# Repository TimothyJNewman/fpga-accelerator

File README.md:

# fpga-accelerator
Creating an FPGA image processor using the Lattice Crosslink-NX LIFCL-40 FPGA. The form factor is a raspberry pi hat.

Using KICAD version 7.

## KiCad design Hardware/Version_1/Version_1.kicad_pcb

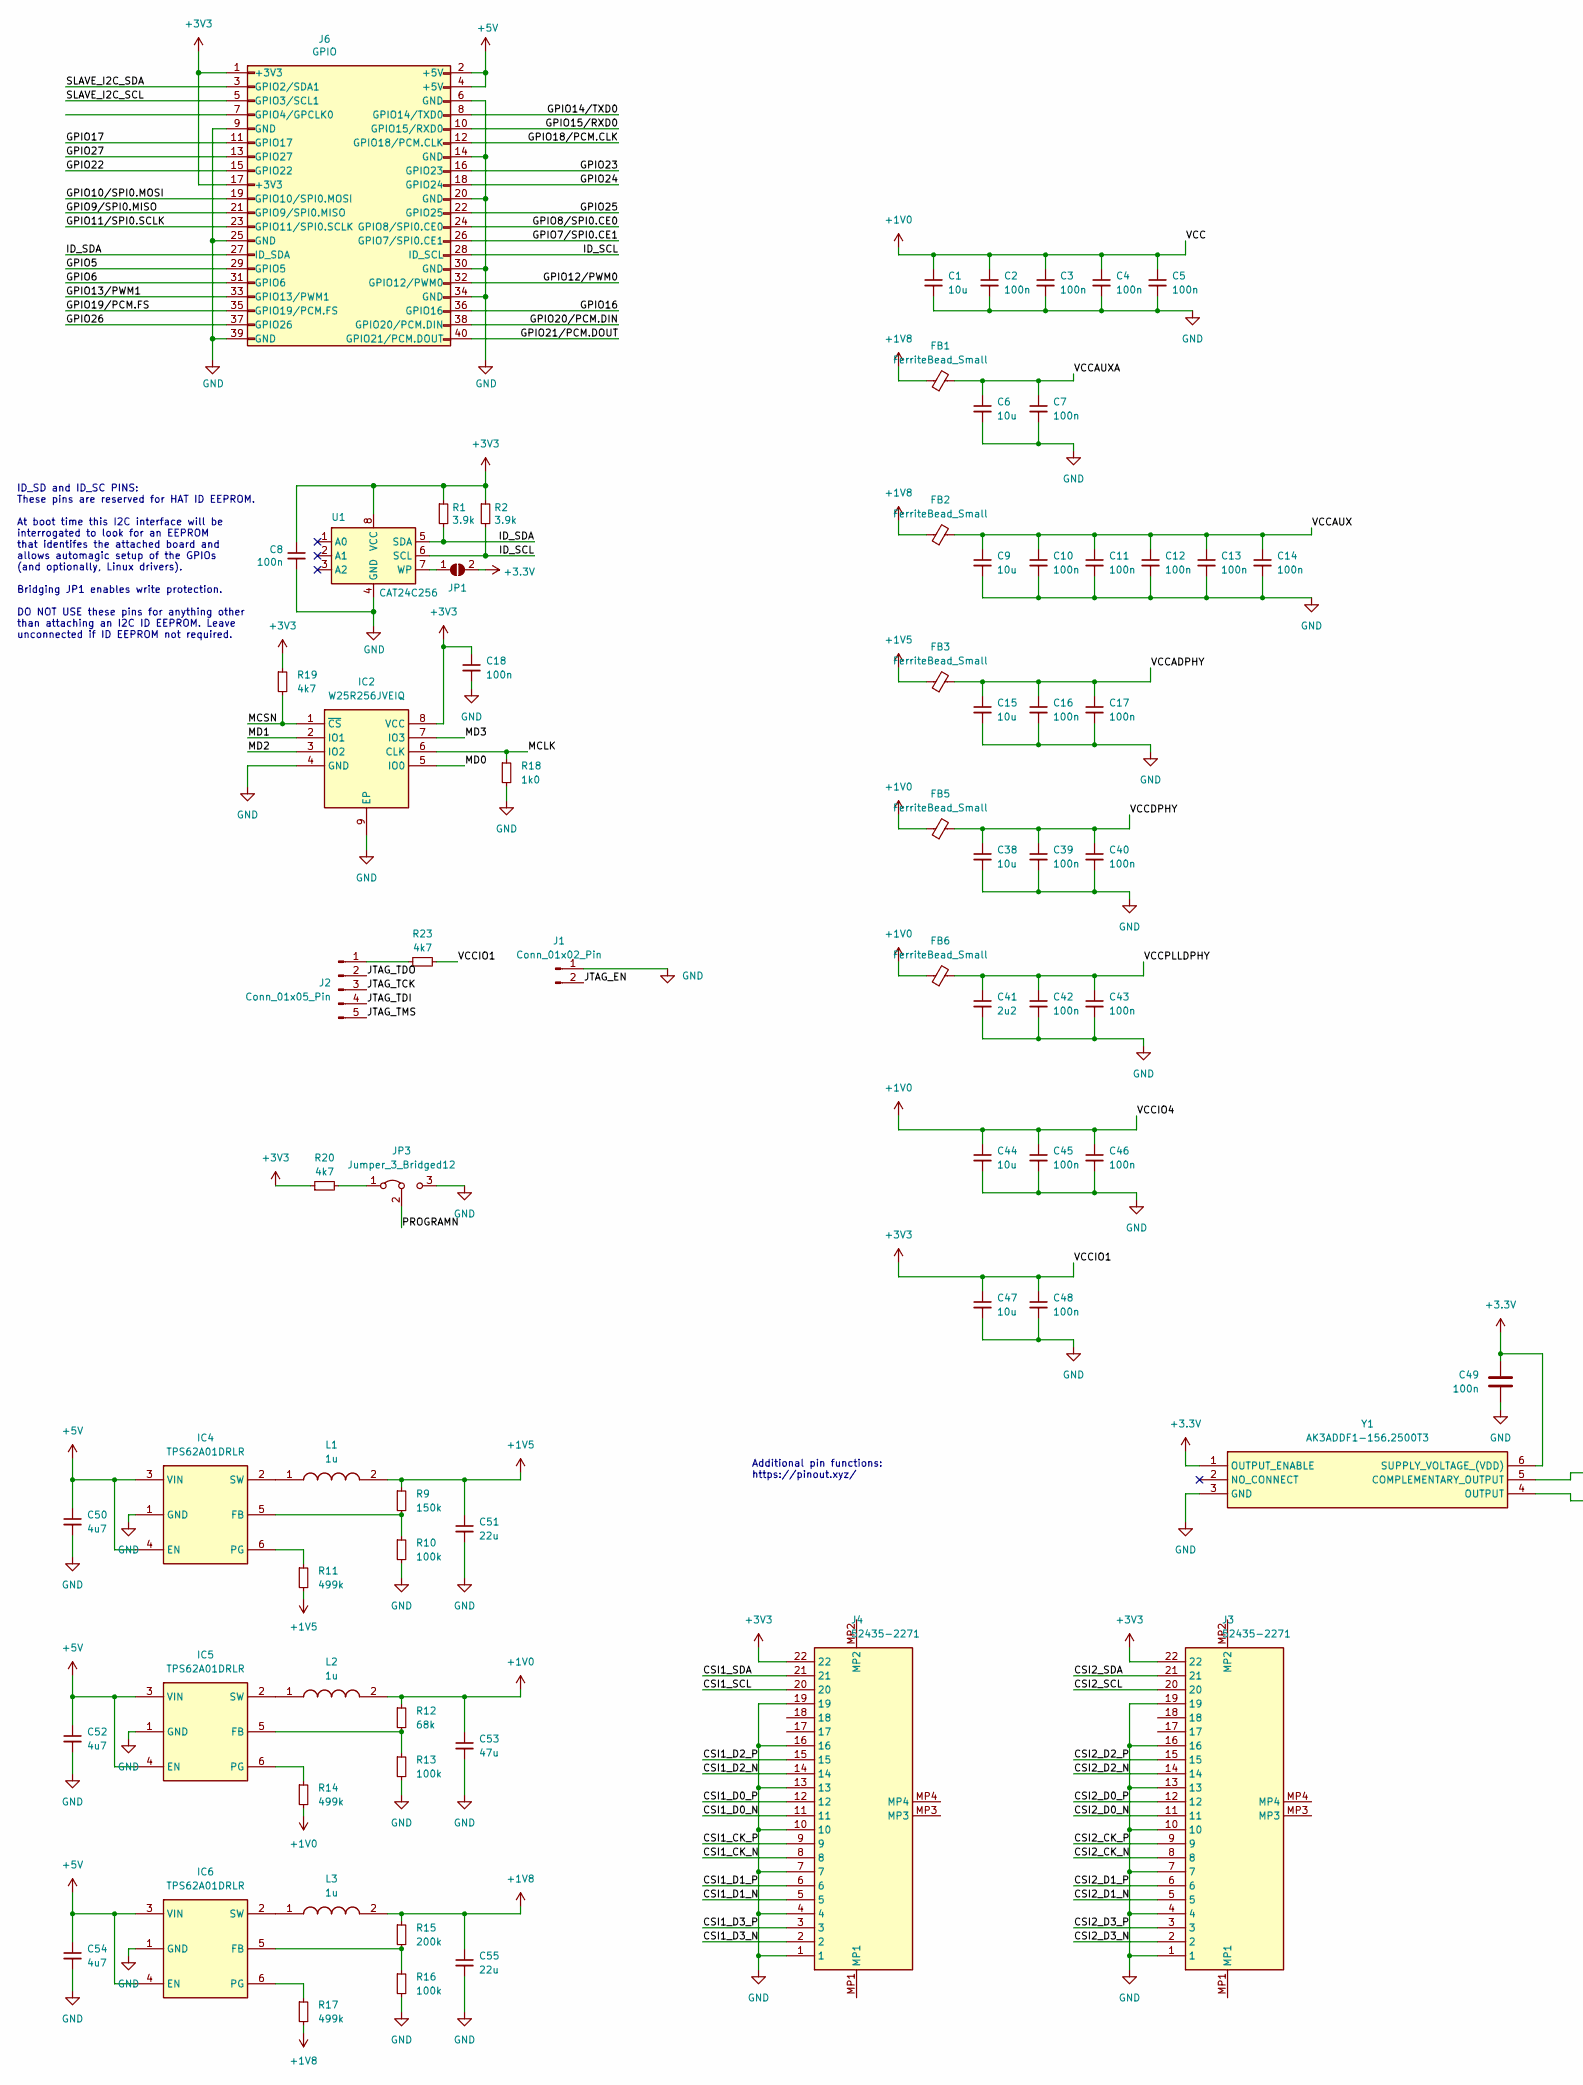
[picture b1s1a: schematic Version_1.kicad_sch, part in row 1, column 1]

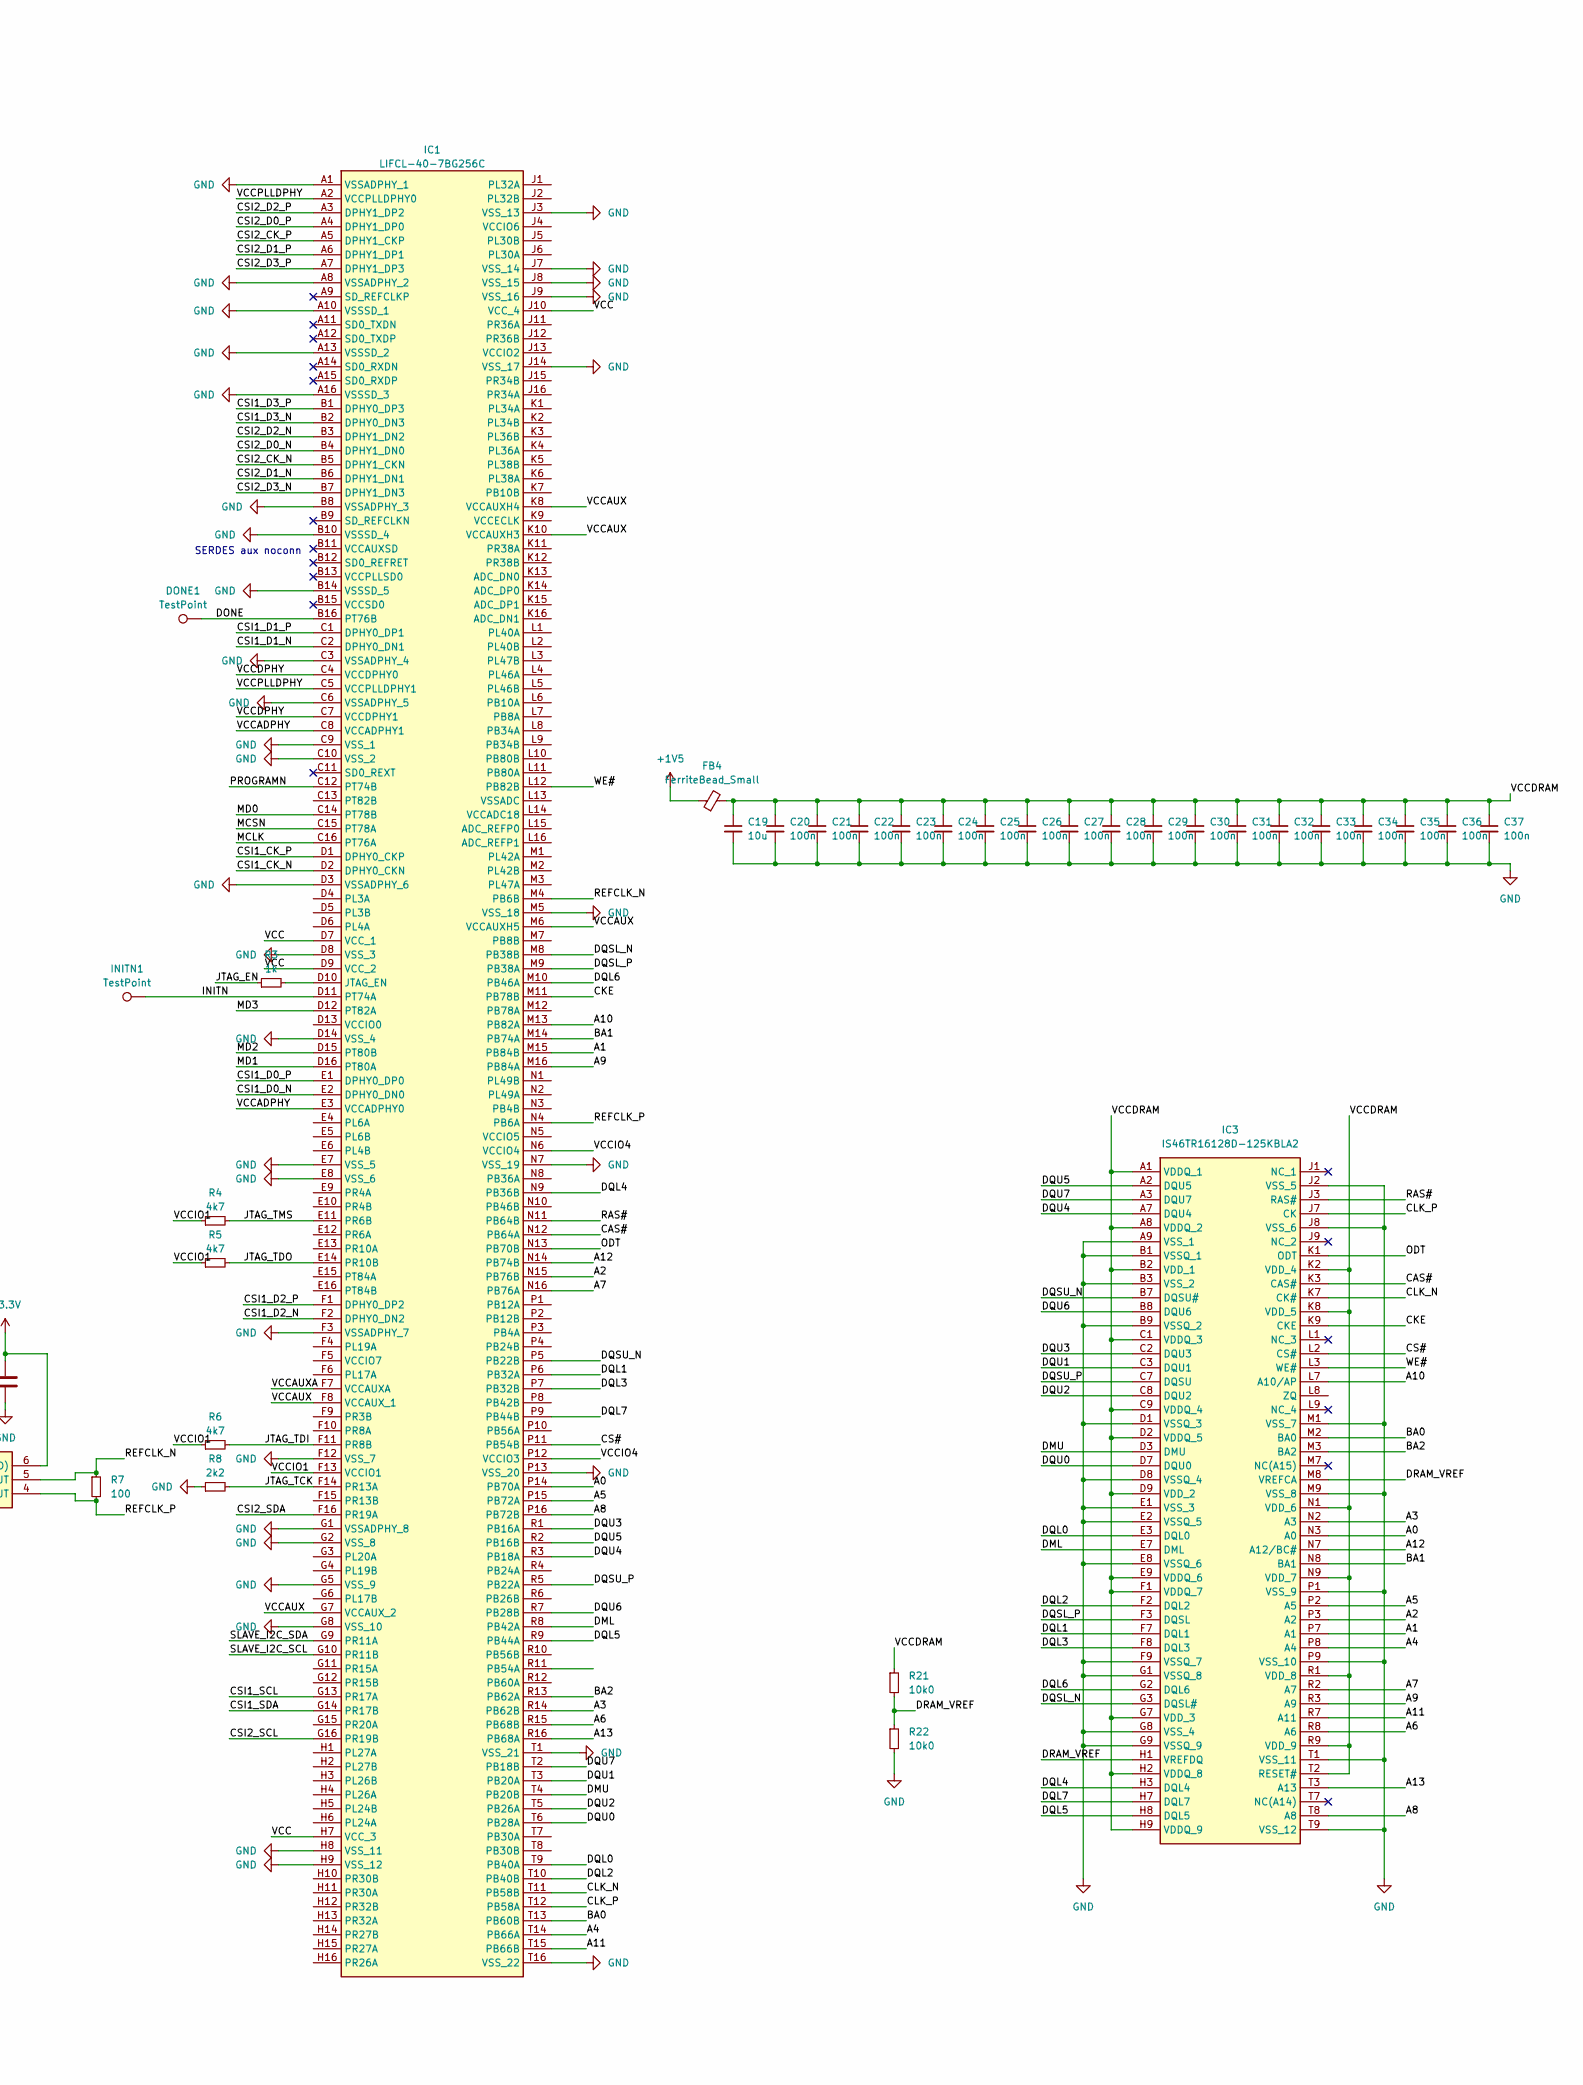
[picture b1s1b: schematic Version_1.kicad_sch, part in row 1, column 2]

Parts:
C1, C6, C15, C19, C38, C44, C47: 10u; C_0402_1005Metric
C2, C3, C4, C5, C7, C10, C11, C12, C13, C14, C16, C17, C20, C21, C22, C23, C24, C25, C26, C27, C28, C29, C30, C31, C32, C33, C34, C35, C36, C37, C39, C40, C42, C43, C45, C46, C48, C49: 100n; C_0402_1005Metric
C8, C18: 100n; C_0603_1608Metric
C9: 10u; C_0603_1608Metric
C41: 2u2; C_0402_1005Metric
C50, C52, C54: 4u7; C_0603_1608Metric
C51, C55: 22u; C_0603_1608Metric
C53: 47u; C_0603_1608Metric
DONE1: TestPoint; TestPoint_Pad_D1.0mm
FB1, FB2, FB3, FB4, FB5, FB6: FerriteBead_Small; C_0805_2012Metric
IC1: LIFCL-40-7BG256C; BGA256C80P16X16_1400X1400X170; Manufacturer_Part_Number LIFCL-40-7BG256C; Mouser Part Number 842-LIFCL-40-7BG256C
IC2: W25R256JVEIQ; SON127P800X600X80-9N-D; Manufacturer_Part_Number W25R256JVEIQ; Mouser Part Number 454-W25R256JVEIQ
IC3: IS46TR16128D-125KBLA2; BGA96C80P9X16_900X1300X120; Manufacturer_Part_Number IS46TR16128D-125KBLA2; Mouser Part Number 870-46T16128D125KBA2
IC4, IC5, IC6: TPS62A01DRLR; SOTFL50P160X60-6N; Manufacturer_Part_Number TPS62A01DRLR; Mouser Part Number 595-TPS62A01DRLR
INITN1: TestPoint; TestPoint_Pad_D1.0mm
J1: Conn_01x02_Pin; PinHeader_1x02_P2.54mm_Vertical
J2: Conn_01x05_Pin; PinHeader_1x05_P2.54mm_Vertical
J3, J4: 52435-2271; 524352271; Manufacturer_Part_Number 52435-2271; Mouser Part Number 538-52435-2271
J6: GPIO; PinSocket_2x20_P2.54mm_Vertical
JP1: ID_WP; SolderJumper-2_P1.3mm_Open_TrianglePad1.0x1.5mm
JP3: Jumper_3_Bridged12; PinHeader_1x03_P2.54mm_Vertical
L1, L2, L3: 1u; DFE2HCAH1R0MJ0L; Manufacturer_Part_Number DFE252012F-1R0M=P2; Mouser Part Number 81-DFE252012F-1R0MP2
R1, R2: 3.9k; R_0603_1608Metric
R3: 1k; R_0402_1005Metric
R4, R5, R6: 4k7; R_0402_1005Metric
R7: 100; R_0603_1608Metric
R8: 2k2; R_0402_1005Metric
R9: 150k; C_0603_1608Metric
R10, R13, R16: 100k; C_0603_1608Metric
R11, R14, R17: 499k; C_0603_1608Metric
R12: 68k; C_0603_1608Metric
R15: 200k; C_0603_1608Metric
R18: 1k0; R_0603_1608Metric
R19, R20, R23: 4k7; R_0603_1608Metric
R21, R22: 10k0; R_0402_1005Metric
U1: CAT24C256; SOP65P640X120-8N
Y1: AK3ADDF1-156.2500T3; AK3ADDF11562500T3; Manufacturer_Part_Number AK3ADDF1-156.2500T3; Mouser Part Number 815-AK3ADF11562500T3

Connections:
+1V0: C1.1, C2.1, C3.1, C4.1, C5.1, C44.1, C45.1, C46.1, C53.1, FB5.1, FB6.1, IC1.D7 (VCC_1), IC1.D9 (VCC_2), IC1.H7 (VCC_3), IC1.J10 (VCC_4), IC1.N6 (VCCIO4), IC1.P12 (VCCIO3), L2.2, R12.1, R14.2
+1V5: C51.1, FB3.1, FB4.1, L1.2, R9.1, R11.2
+1V8: C55.1, FB1.1, FB2.1, L3.2, R15.1, R17.2
+5V: C50.1, C52.1, C54.1, IC4.3 (VIN), IC4.4 (EN), IC5.3 (VIN), IC5.4 (EN), IC6.3 (VIN), IC6.4 (EN), J6.2 (+5V), J6.4 (+5V)
/A0: IC1.P14 (PB70A), IC3.N3 (A0)
/A1: IC1.M15 (PB84B), IC3.P7 (A1)
/A2: IC1.N15 (PB76B), IC3.P3 (A2)
/A3: IC1.R14 (PB62B), IC3.N2 (A3)
/A4: IC1.T14 (PB66A), IC3.P8 (A4)
/A5: IC1.P15 (PB72A), IC3.P2 (A5)
/A6: IC1.R15 (PB68B), IC3.R8 (A6)
/A7: IC1.N16 (PB76A), IC3.R2 (A7)
/A8: IC1.P16 (PB72B), IC3.T8 (A8)
/A9: IC1.M16 (PB84A), IC3.R3 (A9)
/A10: IC1.M13 (PB82A), IC3.L7 (A10/AP)
/A11: IC1.T15 (PB66B), IC3.R7 (A11)
/A12: IC1.N14 (PB74B), IC3.N7 (A12/BC#)
/A13: IC1.R16 (PB68A), IC3.T3 (A13)
/BA0: IC1.T13 (PB60B), IC3.M2 (BA0)
/BA1: IC1.M14 (PB74A), IC3.N8 (BA1)
/BA2: IC1.R13 (PB62A), IC3.M3 (BA2)
/CAS#: IC1.N12 (PB64A), IC3.K3 (CAS#)
/CKE: IC1.M11 (PB78B), IC3.K9 (CKE)
/CLK_N: IC1.T11 (PB58B), IC3.K7 (CK#)
/CLK_P: IC1.T12 (PB58A), IC3.J7 (CK)
/CS#: IC1.P11 (PB54B), IC3.L2 (CS#)
/CSI1_CK_N: IC1.D2 (DPHY0_CKN), J4.8
/CSI1_CK_P: IC1.D1 (DPHY0_CKP), J4.9
/CSI1_D0_N: IC1.E2 (DPHY0_DN0), J4.11
/CSI1_D0_P: IC1.E1 (DPHY0_DP0), J4.12
/CSI1_D1_N: IC1.C2 (DPHY0_DN1), J4.5
/CSI1_D1_P: IC1.C1 (DPHY0_DP1), J4.6
/CSI1_D2_N: IC1.F2 (DPHY0_DN2), J4.14
/CSI1_D2_P: IC1.F1 (DPHY0_DP2), J4.15
/CSI1_D3_N: IC1.B2 (DPHY0_DN3), J4.2
/CSI1_D3_P: IC1.B1 (DPHY0_DP3), J4.3
/CSI1_SCL: IC1.G13 (PR17A), J4.20
/CSI1_SDA: IC1.G14 (PR17B), J4.21
/CSI2_CK_N: IC1.B5 (DPHY1_CKN), J3.8
/CSI2_CK_P: IC1.A5 (DPHY1_CKP), J3.9
/CSI2_D0_N: IC1.B4 (DPHY1_DN0), J3.11
/CSI2_D0_P: IC1.A4 (DPHY1_DP0), J3.12
/CSI2_D1_N: IC1.B6 (DPHY1_DN1), J3.5
/CSI2_D1_P: IC1.A6 (DPHY1_DP1), J3.6
/CSI2_D2_N: IC1.B3 (DPHY1_DN2), J3.14
/CSI2_D2_P: IC1.A3 (DPHY1_DP2), J3.15
/CSI2_D3_N: IC1.B7 (DPHY1_DN3), J3.2
/CSI2_D3_P: IC1.A7 (DPHY1_DP3), J3.3
/CSI2_SCL: IC1.G16 (PR19B), J3.20
/CSI2_SDA: IC1.F16 (PR19A), J3.21
/DML: IC1.R8 (PB42A), IC3.E7 (DML)
/DMU: IC1.T4 (PB20B), IC3.D3 (DMU)
/DONE: DONE1.1, IC1.B16 (PT76B)
/DQL0: IC1.T9 (PB40A), IC3.E3 (DQL0)
/DQL1: IC1.P6 (PB32A), IC3.F7 (DQL1)
/DQL2: IC1.T10 (PB40B), IC3.F2 (DQL2)
/DQL3: IC1.P7 (PB32B), IC3.F8 (DQL3)
/DQL4: IC1.N9 (PB36B), IC3.H3 (DQL4)
/DQL5: IC1.R9 (PB44A), IC3.H8 (DQL5)
/DQL6: IC1.M10 (PB46A), IC3.G2 (DQL6)
/DQL7: IC1.P9 (PB44B), IC3.H7 (DQL7)
/DQSL_N: IC1.M8 (PB38B), IC3.G3 (DQSL#)
/DQSL_P: IC1.M9 (PB38A), IC3.F3 (DQSL)
/DQSU_N: IC1.P5 (PB22B), IC3.B7 (DQSU#)
/DQSU_P: IC1.R5 (PB22A), IC3.C7 (DQSU)
/DQU0: IC1.T6 (PB28A), IC3.D7 (DQU0)
/DQU1: IC1.T3 (PB20A), IC3.C3 (DQU1)
/DQU2: IC1.T5 (PB26A), IC3.C8 (DQU2)
/DQU3: IC1.R1 (PB16A), IC3.C2 (DQU3)
/DQU4: IC1.R3 (PB18A), IC3.A7 (DQU4)
/DQU5: IC1.R2 (PB16B), IC3.A2 (DQU5)
/DQU6: IC1.R7 (PB28B), IC3.B8 (DQU6)
/DQU7: IC1.T2 (PB18B), IC3.A3 (DQU7)
/DRAM_VREF: IC3.H1 (VREFDQ), IC3.M8 (VREFCA), R21.2, R22.1
/GPIO5: J6.29 (GPIO5)
/GPIO6: J6.31 (GPIO6)
/GPIO7/SPI0.CE1: J6.26 (GPIO7/SPI0.CE1)
/GPIO8/SPI0.CE0: J6.24 (GPIO8/SPI0.CE0)
/GPIO9/SPI0.MISO: J6.21 (GPIO9/SPI0.MISO)
/GPIO10/SPI0.MOSI: J6.19 (GPIO10/SPI0.MOSI)
/GPIO11/SPI0.SCLK: J6.23 (GPIO11/SPI0.SCLK)
/GPIO12/PWM0: J6.32 (GPIO12/PWM0)
/GPIO13/PWM1: J6.33 (GPIO13/PWM1)
/GPIO14/TXD0: J6.8 (GPIO14/TXD0)
/GPIO15/RXD0: J6.10 (GPIO15/RXD0)
/GPIO16: J6.36 (GPIO16)
/GPIO17: J6.11 (GPIO17)
/GPIO18/PCM.CLK: J6.12 (GPIO18/PCM.CLK)
/GPIO19/PCM.FS: J6.35 (GPIO19/PCM.FS)
/GPIO20/PCM.DIN: J6.38 (GPIO20/PCM.DIN)
/GPIO21/PCM.DOUT: J6.40 (GPIO21/PCM.DOUT)
/GPIO22: J6.15 (GPIO22)
/GPIO23: J6.16 (GPIO23)
/GPIO24: J6.18 (GPIO24)
/GPIO25: J6.22 (GPIO25)
/GPIO26: J6.37 (GPIO26)
/GPIO27: J6.13 (GPIO27)
/ID_SCL: J6.28 (ID_SCL), R2.2, U1.6 (SCL)
/ID_SDA: J6.27 (ID_SDA), R1.2, U1.5 (SDA)
/INITN: IC1.D11 (PT74A), INITN1.1
/JTAG_EN: J1.2, R3.1
/JTAG_TCK: IC1.F14 (PR13A), J2.3, R8.2
/JTAG_TDI: IC1.F11 (PR8B), J2.4, R6.2
/JTAG_TDO: IC1.E14 (PR10B), J2.2, R5.2
/JTAG_TMS: IC1.E11 (PR6B), J2.5, R4.2
/MCLK: IC1.C16 (PT76A), IC2.6 (CLK), R18.1
/MCSN: IC1.C15 (PT78A), IC2.1 (~CS), R19.2
/MD0: IC1.C14 (PT78B), IC2.5 (IO0)
/MD1: IC1.D16 (PT80A), IC2.2 (IO1)
/MD2: IC1.D15 (PT80B), IC2.3 (IO2)
/MD3: IC1.D12 (PT82A), IC2.7 (IO3)
/ODT: IC1.N13 (PB70B), IC3.K1 (ODT)
/PROGRAMN: IC1.C12 (PT74B), JP3.2 (C)
/RAS#: IC1.N11 (PB64B), IC3.J3 (RAS#)
/REFCLK_N: IC1.M4 (PB6B), R7.1, Y1.5 (COMPLEMENTARY_OUTPUT)
/REFCLK_P: IC1.N4 (PB6A), R7.2, Y1.4 (OUTPUT)
/SLAVE_I2C_SCL: IC1.G10 (PR11B), J6.5 (GPIO3/SCL1)
/SLAVE_I2C_SDA: IC1.G9 (PR11A), J6.3 (GPIO2/SDA1)
/VCCADPHY: C15.1, C16.1, C17.1, FB3.2, IC1.C8 (VCCADPHY1), IC1.E3 (VCCADPHY0)
/VCCAUX: C9.1, C10.1, C11.1, C12.1, C13.1, C14.1, FB2.2, IC1.F8 (VCCAUX_1), IC1.G7 (VCCAUX_2), IC1.K8 (VCCAUXH4), IC1.K10 (VCCAUXH3), IC1.M6 (VCCAUXH5)
/VCCAUXA: C6.1, C7.1, FB1.2, IC1.F7 (VCCAUXA)
/VCCDPHY: C38.1, C39.1, C40.1, FB5.2, IC1.C4 (VCCDPHY0), IC1.C7 (VCCDPHY1)
/VCCDRAM: C19.1, C20.1, C21.1, C22.1, C23.1, C24.1, C25.1, C26.1, C27.1, C28.1, C29.1, C30.1, C31.1, C32.1, C33.1, C34.1, C35.1, C36.1, C37.1, FB4.2, IC3.A1 (VDDQ_1), IC3.A8 (VDDQ_2), IC3.B2 (VDD_1), IC3.C1 (VDDQ_3), IC3.C9 (VDDQ_4), IC3.D2 (VDDQ_5), IC3.D9 (VDD_2), IC3.E9 (VDDQ_6), IC3.F1 (VDDQ_7), IC3.G7 (VDD_3), IC3.H2 (VDDQ_8), IC3.H9 (VDDQ_9), IC3.K2 (VDD_4), IC3.K8 (VDD_5), IC3.N1 (VDD_6), IC3.N9 (VDD_7), IC3.R1 (VDD_8), IC3.R9 (VDD_9), IC3.T2 (RESET#), R21.1
/VCCPLLDPHY: C41.1, C42.1, C43.1, FB6.2, IC1.A2 (VCCPLLDPHY0), IC1.C5 (VCCPLLDPHY1)
/WE#: IC1.L12 (PB82B), IC3.L3 (WE#)
GND: C1.2, C2.2, C3.2, C4.2, C5.2, C6.2, C7.2, C8.2, C9.2, C10.2, C11.2, C12.2, C13.2, C14.2, C15.2, C16.2, C17.2, C18.2, C19.2, C20.2, C21.2, C22.2, C23.2, C24.2, C25.2, C26.2, C27.2, C28.2, C29.2, C30.2, C31.2, C32.2, C33.2, C34.2, C35.2, C36.2, C37.2, C38.2, C39.2, C40.2, C41.2, C42.2, C43.2, C44.2, C45.2, C46.2, C47.2, C48.2, C49.2, C50.2, C51.2, C52.2, C53.2, C54.2, C55.2, IC1.A1 (VSSADPHY_1), IC1.A8 (VSSADPHY_2), IC1.A10 (VSSSD_1), IC1.A13 (VSSSD_2), IC1.A16 (VSSSD_3), IC1.B8 (VSSADPHY_3), IC1.B10 (VSSSD_4), IC1.B14 (VSSSD_5), IC1.C3 (VSSADPHY_4), IC1.C6 (VSSADPHY_5), IC1.C9 (VSS_1), IC1.C10 (VSS_2), IC1.D3 (VSSADPHY_6), IC1.D8 (VSS_3), IC1.D14 (VSS_4), IC1.E7 (VSS_5), IC1.E8 (VSS_6), IC1.F3 (VSSADPHY_7), IC1.F12 (VSS_7), IC1.G1 (VSSADPHY_8), IC1.G2 (VSS_8), IC1.G5 (VSS_9), IC1.G8 (VSS_10), IC1.H8 (VSS_11), IC1.H9 (VSS_12), IC1.J3 (VSS_13), IC1.J7 (VSS_14), IC1.J8 (VSS_15), IC1.J9 (VSS_16), IC1.J14 (VSS_17), IC1.M5 (VSS_18), IC1.N7 (VSS_19), IC1.P13 (VSS_20), IC1.T1 (VSS_21), IC1.T16 (VSS_22), IC2.4 (GND), IC2.9 (EP), IC3.A9 (VSS_1), IC3.B1 (VSSQ_1), IC3.B3 (VSS_2), IC3.B9 (VSSQ_2), IC3.D1 (VSSQ_3), IC3.D8 (VSSQ_4), IC3.E1 (VSS_3), IC3.E2 (VSSQ_5), IC3.E8 (VSSQ_6), IC3.F9 (VSSQ_7), IC3.G1 (VSSQ_8), IC3.G8 (VSS_4), IC3.G9 (VSSQ_9), IC3.J2 (VSS_5), IC3.J8 (VSS_6), IC3.M1 (VSS_7), IC3.M9 (VSS_8), IC3.P1 (VSS_9), IC3.P9 (VSS_10), IC3.T1 (VSS_11), IC3.T9 (VSS_12), IC4.1 (GND), IC5.1 (GND), IC6.1 (GND), J1.1, J3.1, J3.4, J3.7, J3.10, J3.13, J3.16, J3.19, J4.1, J4.4, J4.7, J4.10, J4.13, J4.16, J4.19, J6.6 (GND), J6.9 (GND), J6.14 (GND), J6.20 (GND), J6.25 (GND), J6.30 (GND), J6.34 (GND), J6.39 (GND), JP3.3 (B), R8.1, R10.2, R13.2, R16.2, R18.2, R22.2, U1.4 (GND), Y1.3 (GND)
unnamed: IC1.D10 (JTAG_EN), R3.2
unnamed: IC4.5 (FB), R9.2, R10.1
unnamed: IC4.6 (PG), R11.1
unnamed: IC4.2 (SW), L1.1
unnamed: IC5.5 (FB), R12.2, R13.1
unnamed: IC5.6 (PG), R14.1
unnamed: IC5.2 (SW), L2.1
unnamed: IC6.5 (FB), R15.2, R16.1
unnamed: IC6.6 (PG), R17.1
unnamed: IC6.2 (SW), L3.1
unnamed: J2.1, R23.1
unnamed: JP1.1 (A), U1.7 (WP)
unnamed: JP3.1 (A), R20.2

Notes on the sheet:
SERDES aux noconn
ID_SD and ID_SC PINS: These pins are reserved for HAT ID EEPROM. At boot time this I2C interface will be interrogated to look for an EEPROM that identifes the attached board and allows automagic setup of the GPIOs (and optionally, Linux drivers). Bridging JP1 enables write protection. DO NOT USE th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
Additional pin functions: https://pinout.xyz/

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
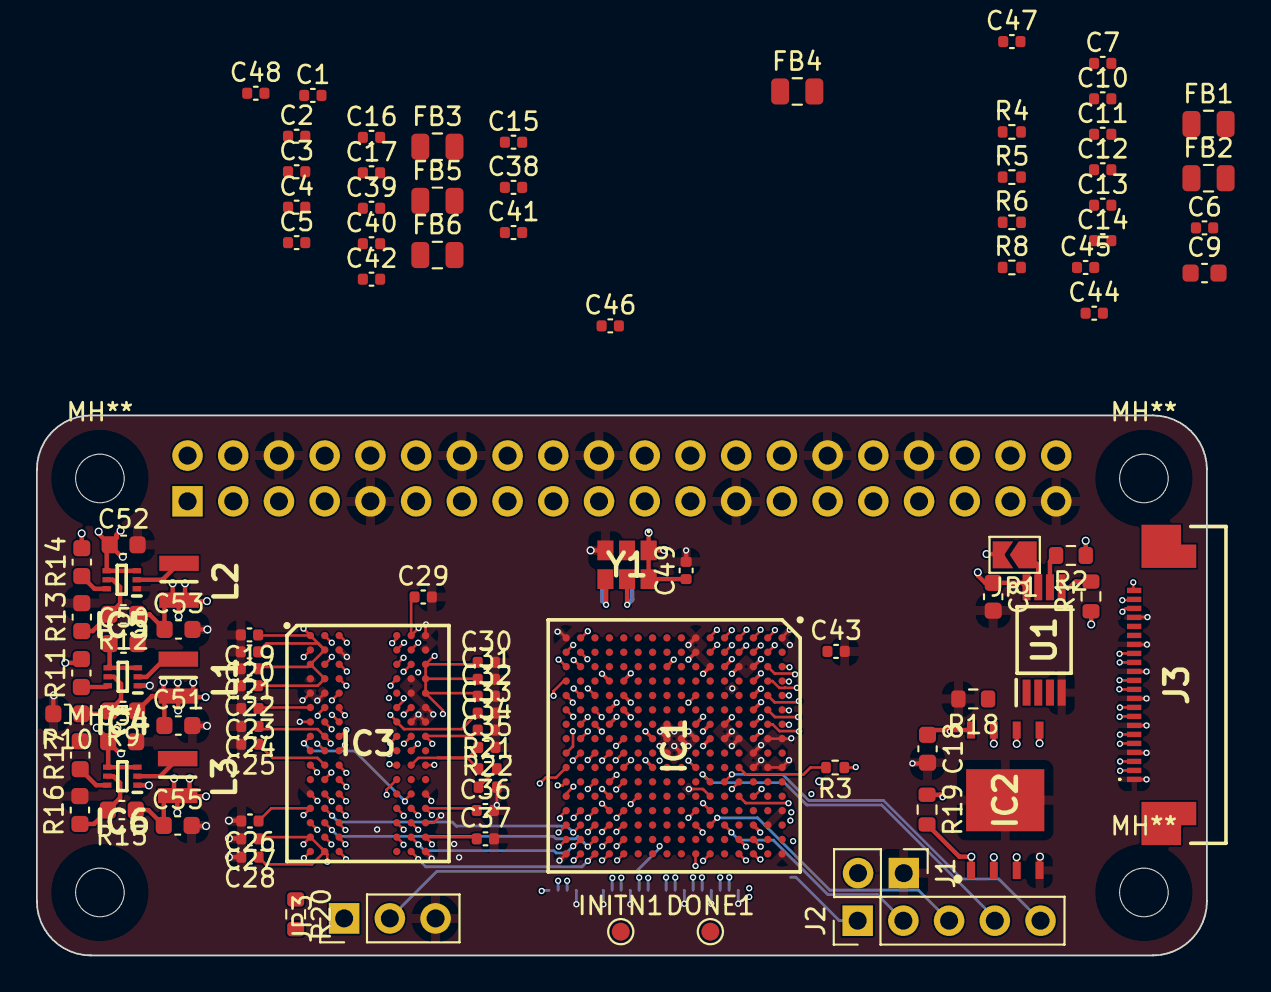
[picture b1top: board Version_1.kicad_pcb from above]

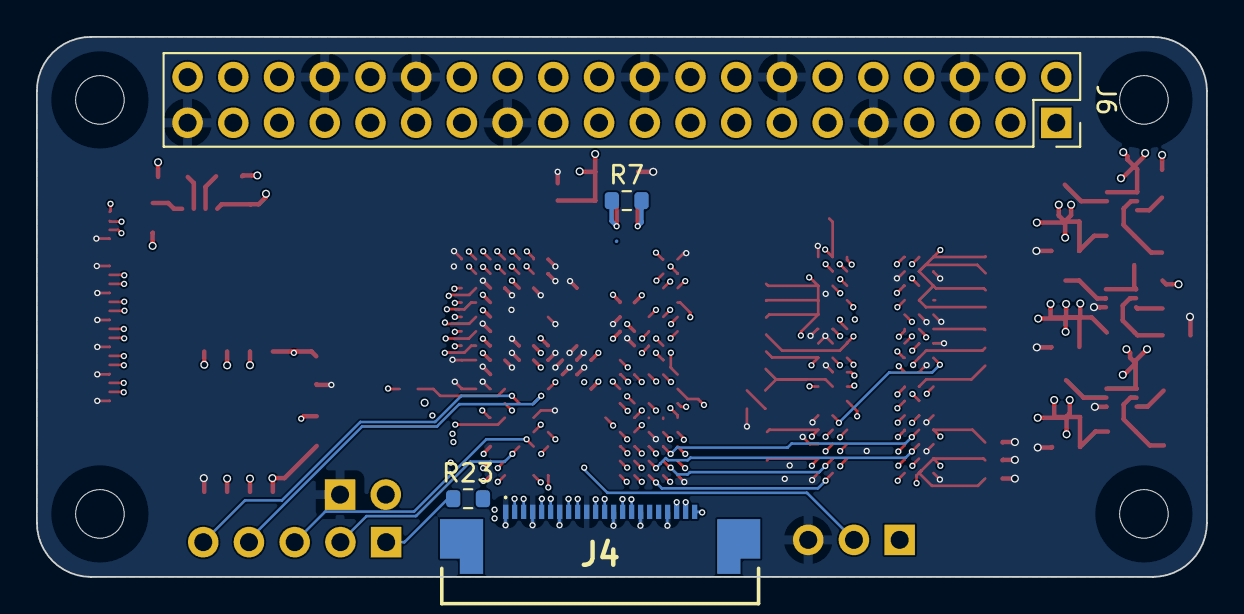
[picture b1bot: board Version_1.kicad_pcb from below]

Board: 6 copper layers, 65.0 x 30.0 mm, 108 parts (4 on the bottom side), 117 nets.

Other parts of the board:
MH**: MountingHole_2.7mm
MH**#2, MH**#3, MH**#4: MountingHole_2.7mm

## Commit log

2023-10-02 Added pins in lattice radiant. Need to rearrange
2023-10-02 added pll
2023-10-03 Done routing for first DQS group
2023-10-03 DRAM DQ groups
2023-10-04 Redid routing with custom meadering paramters
2023-10-06 Started routing DDR address lines
2023-10-06 Tried importing project into altium
2023-10-06 Changed gitignore to ignore zip files
2023-10-07 mipi routing
2023-10-08 Added i2c and flash chip
2023-10-10 Layout for JTAG
2023-10-10 Added decoupling c for DRAM
